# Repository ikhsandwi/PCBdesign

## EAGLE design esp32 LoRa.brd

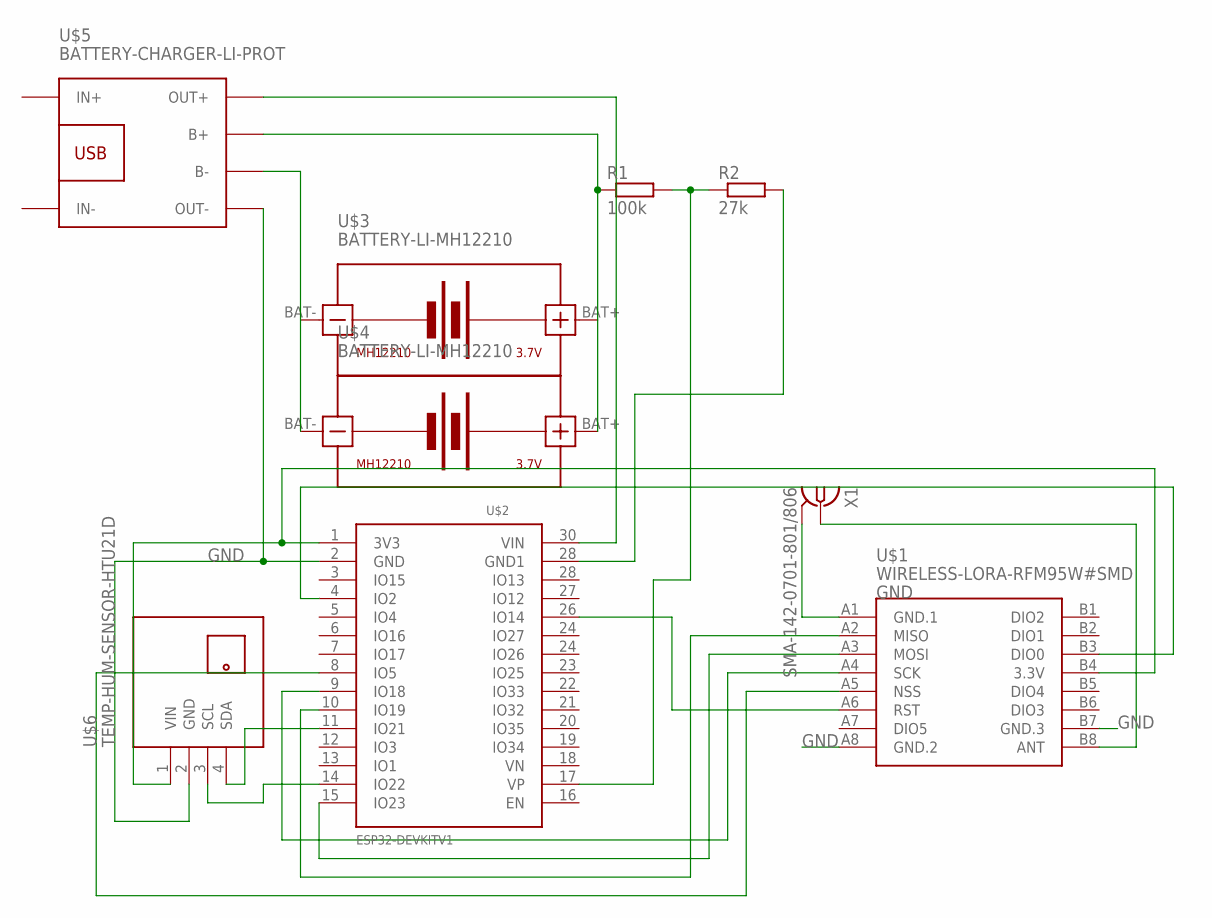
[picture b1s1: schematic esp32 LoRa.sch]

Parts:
R1: 100k; 0204/7
R2: 27k; 0204/7
U$1: WIRELESS-LORA-RFM95W#SMD
U$2: ESP32DEVKITV1; ESP32-DEVKITV1
U$3, U$4: BATTERY-LI-MH12210
U$5: BATTERY-CHARGER-LI-PROT
U$6: TEMP-HUM-SENSOR-HTU21D
X1: SMA-142-0701-801/806; J502-ND-142-0701-801/806

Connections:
GND: U$1.A1 (GND.1), U$1.A8 (GND.2), U$1.B7 (GND.3), U$2.2 (GND), U$5.OUT-, U$6.2 (GND), X1.G@1 (2), X1.G@2 (2), X1.G@3 (2), X1.G@4 (2)
unnamed: U$1.B4 (3.3V), U$2.1 (3V3), U$6.1 (VIN)
unnamed: R2.2, U$2.28 (IO13)
unnamed: U$2.14 (IO22), U$6.3 (SCL)
unnamed: U$2.11 (IO21), U$6.4 (SDA)
unnamed: U$3.BAT-, U$4.BAT-, U$5.B-
unnamed: R1.1, U$3.BAT+, U$4.BAT+, U$5.B+
unnamed: U$2.30 (VIN), U$5.OUT+
unnamed: U$1.A2 (MISO), U$2.10 (IO19)
unnamed: U$1.A3 (MOSI), U$2.15 (IO23)
unnamed: U$1.A4 (SCK), U$2.9 (IO18)
unnamed: U$1.B3 (DIO0), U$2.4 (IO2)
unnamed: U$1.A6 (RST), U$2.26 (IO14)
unnamed: U$1.A5 (NSS), U$2.8 (IO5)
unnamed: U$1.B8 (ANT), X1.1
unnamed: R1.2, R2.1, U$2.17 (VP)

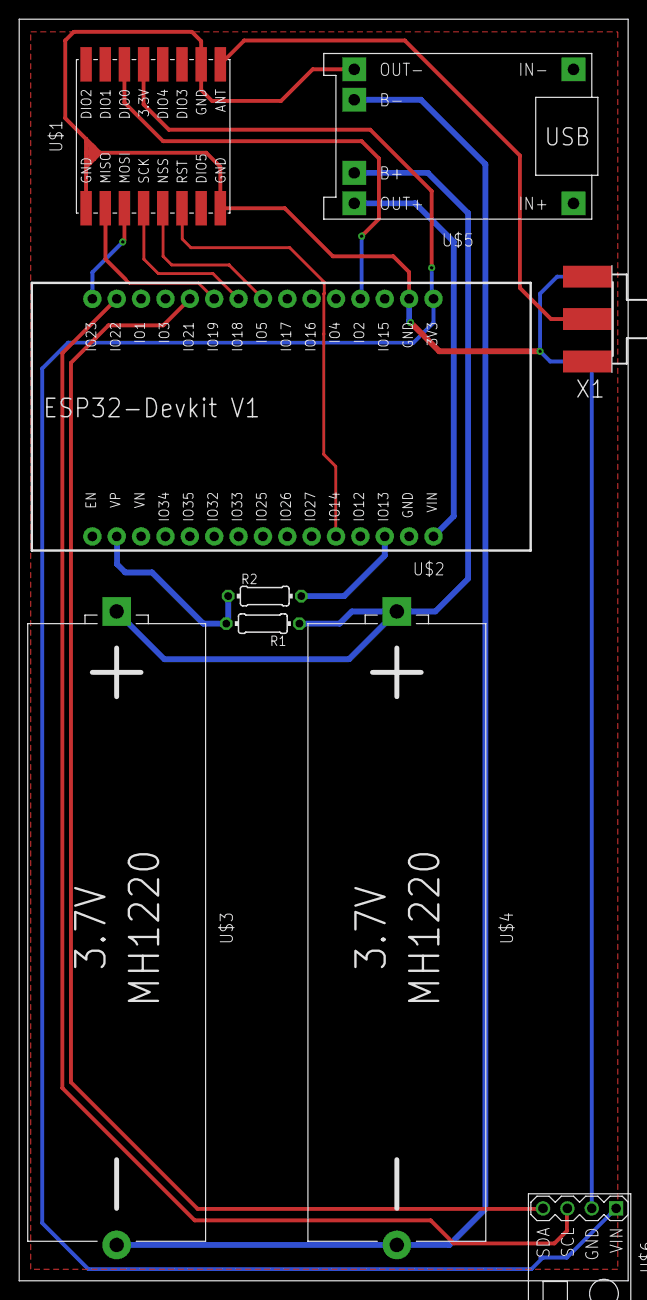
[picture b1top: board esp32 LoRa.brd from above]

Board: 2 copper layers, 63.5 x 131.5 mm, 9 parts (0 on the bottom side), 16 nets.

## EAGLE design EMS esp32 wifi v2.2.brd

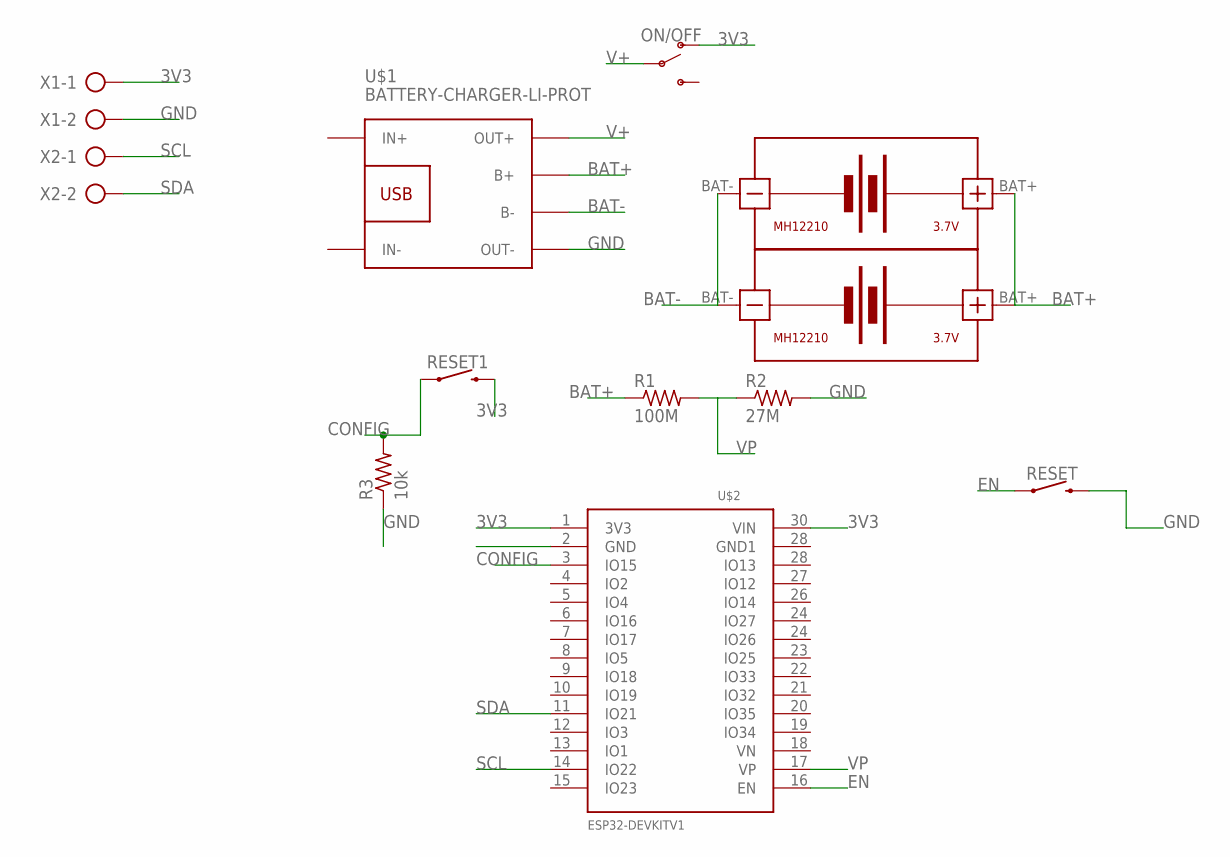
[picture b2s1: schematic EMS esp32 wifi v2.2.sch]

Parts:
ON/OFF: SWITCH-SPDT-PTH-11.6X4.0MM; SWITCH_SPDT_PTH_11.6X4.0MM
R1: 100M; 0204/7
R2: 27M; 0204/7
R3: 10k; 0204/7
RESET, RESET1: MOMENTARY-SWITCH-SPST-PTH-6.0MM; TACTILE_SWITCH_PTH_6.0MM
U$1: BATTERY-CHARGER-LI-PROT
U$2: ESP32DEVKITV1; ESP32-DEVKITV1
U$3, U$4: BATTERY-LI-MH12210
X1, X2: AK500/2

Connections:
3V3: ON/OFF.1 (O), RESET1.3 (2), U$2.1 (3V3), U$2.30 (VIN), X1.1
BAT+: R1.1, U$1.B+, U$3.BAT+, U$4.BAT+
BAT-: U$1.B-, U$3.BAT-, U$4.BAT-
CONFIG: R3.2, RESET1.1, U$2.3 (IO15)
EN: RESET.1, U$2.16 (EN)
GND: R2.2, R3.1, RESET.3 (2), U$1.OUT-, U$2.2 (GND), X1.2
SCL: U$2.14 (IO22), X2.1
SDA: U$2.11 (IO21), X2.2
V+: ON/OFF.2, U$1.OUT+
VP: R1.2, R2.1, U$2.17 (VP)

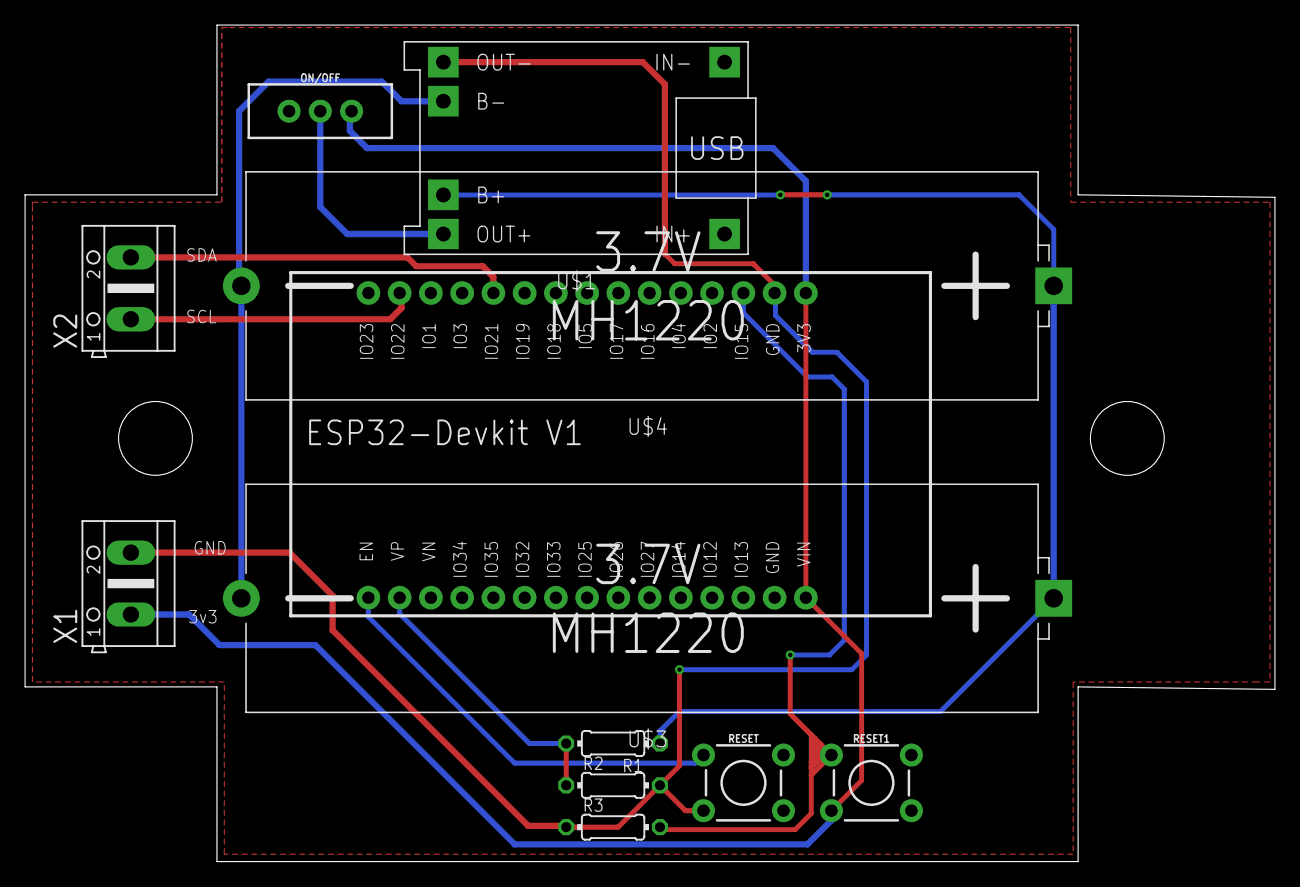
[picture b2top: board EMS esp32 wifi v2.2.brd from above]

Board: 2 copper layers, 101.6 x 68.0 mm, 12 parts (0 on the bottom side), 10 nets.

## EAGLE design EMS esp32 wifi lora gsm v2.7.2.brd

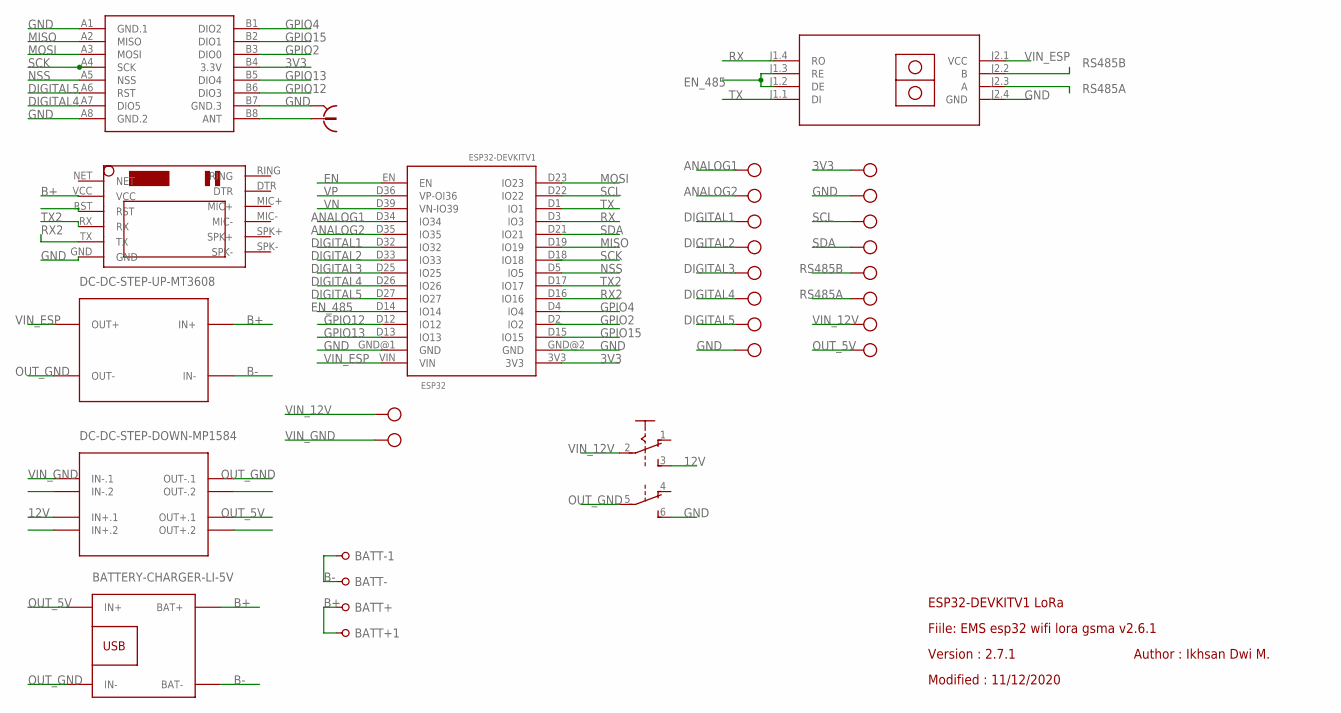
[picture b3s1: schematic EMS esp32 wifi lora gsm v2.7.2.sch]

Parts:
3V3__GND, 12V__5V: MKDSN1,5/2-5,08
A1__A2: MKDSN1,5/2-5,08
A_____B: MKDSN1,5/2-5,08
BATT+, BATT+1: PIN-1X1_2.00; 1X01M
BATT-, BATT-1: PIN-1X1; 1X01NONAME
D1__D2, D3__D4, D5_GND: MKDSN1,5/2-5,08
ESP32: ESP32DEVKITV1; ESP32-DEVKITV1
S1: A68-A31
SCL__SDA: MKDSN1,5/2-5,08
U$1: RS485-TTL-CONVERTER
U$2: DC-DC-STEP-UP-MT3608
U$3: DC-DC-STEP-DOWN-MP1584
U$4: BATTERY-CHARGER-LI-5V
U$5: WIRELESS-LORA-RFM95W#SMD
U$9: SIM800LMODULE
X1: 734120110
X10: MKDSN1,5/2-5,08

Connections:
3V3: 3V3__GND.1, ESP32.3V3, U$5.B4 (3.3V)
12V: S1.3 (S), U$3.IN+.1
ANALOG1: A1__A2.1, ESP32.D34 (IO34)
ANALOG2: A1__A2.2, ESP32.D35 (IO35)
B+: BATT+.1, BATT+1.1, U$2.IN+, U$4.BAT+, U$9.VCC
B-: BATT-.1, BATT-1.1, U$2.IN-, U$4.BAT-
DIGITAL1: D1__D2.1, ESP32.D32 (IO32)
DIGITAL2: D1__D2.2, ESP32.D33 (IO33)
DIGITAL3: D3__D4.1, ESP32.D25 (IO25)
DIGITAL4: D3__D4.2, ESP32.D26 (IO26), U$5.A7 (DIO5)
DIGITAL5: D5_GND.1, ESP32.D27 (IO27), U$5.A6 (RST)
EN: ESP32.EN
EN_485: ESP32.D14 (IO14), U$1.J1.2 (DE), U$1.J1.3 (RE)
GND: 3V3__GND.2, D5_GND.2, ESP32.GND@1 (GND), ESP32.GND@2 (GND), S1.6 (S), U$1.J2.4 (GND), U$5.A1 (GND.1), U$5.A8 (GND.2), U$5.B7 (GND.3), U$9.GND, X1.S@1 (2), X1.S@2 (2), X1.S@3 (2)
GPIO2: ESP32.D2 (IO2), U$5.B3 (DIO0)
GPIO4: ESP32.D4 (IO4), U$5.B1 (DIO2)
GPIO12: ESP32.D12 (IO12), U$5.B6 (DIO3)
GPIO13: ESP32.D13 (IO13), U$5.B5 (DIO4)
GPIO15: ESP32.D15 (IO15), U$5.B2 (DIO1)
MISO: ESP32.D19 (IO19), U$5.A2 (MISO)
MOSI: ESP32.D23 (IO23), U$5.A3 (MOSI)
unnamed: U$5.B8 (ANT), X1.1
NSS: ESP32.D5 (IO5), U$5.A5 (NSS)
OUT_5V: 12V__5V.2, U$3.OUT+.1, U$4.IN+
OUT_GND: S1.5, U$2.OUT-, U$3.OUT-.1, U$4.IN-
RS485A: A_____B.2, U$1.J2.3 (A)
RS485B: A_____B.1, U$1.J2.2 (B)
RX: ESP32.D3 (IO3), U$1.J1.4 (RO)
RX2: ESP32.D16 (IO16), U$9.TX
SCK: ESP32.D18 (IO18), U$5.A4 (SCK)
SCL: ESP32.D22 (IO22), SCL__SDA.1
SDA: ESP32.D21 (IO21), SCL__SDA.2
TX: ESP32.D1 (IO1), U$1.J1.1 (DI)
TX2: ESP32.D17 (IO17), U$9.RX
VIN_12V: 12V__5V.1, S1.2, X10.1
VIN_ESP: ESP32.VIN, U$1.J2.1 (VCC), U$2.OUT+
VIN_GND: U$3.IN-.1, X10.2
VN: ESP32.D39 (VN-IO39)
VP: ESP32.D36 (VP-OI36)

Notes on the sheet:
ESP32-DEVKITV1 LoRa
Fiile: EMS esp32 wifi lora gsma v2.6.1
Version : 2.7.1
Modified : 11/12/2020
Author : Ikhsan Dwi M.

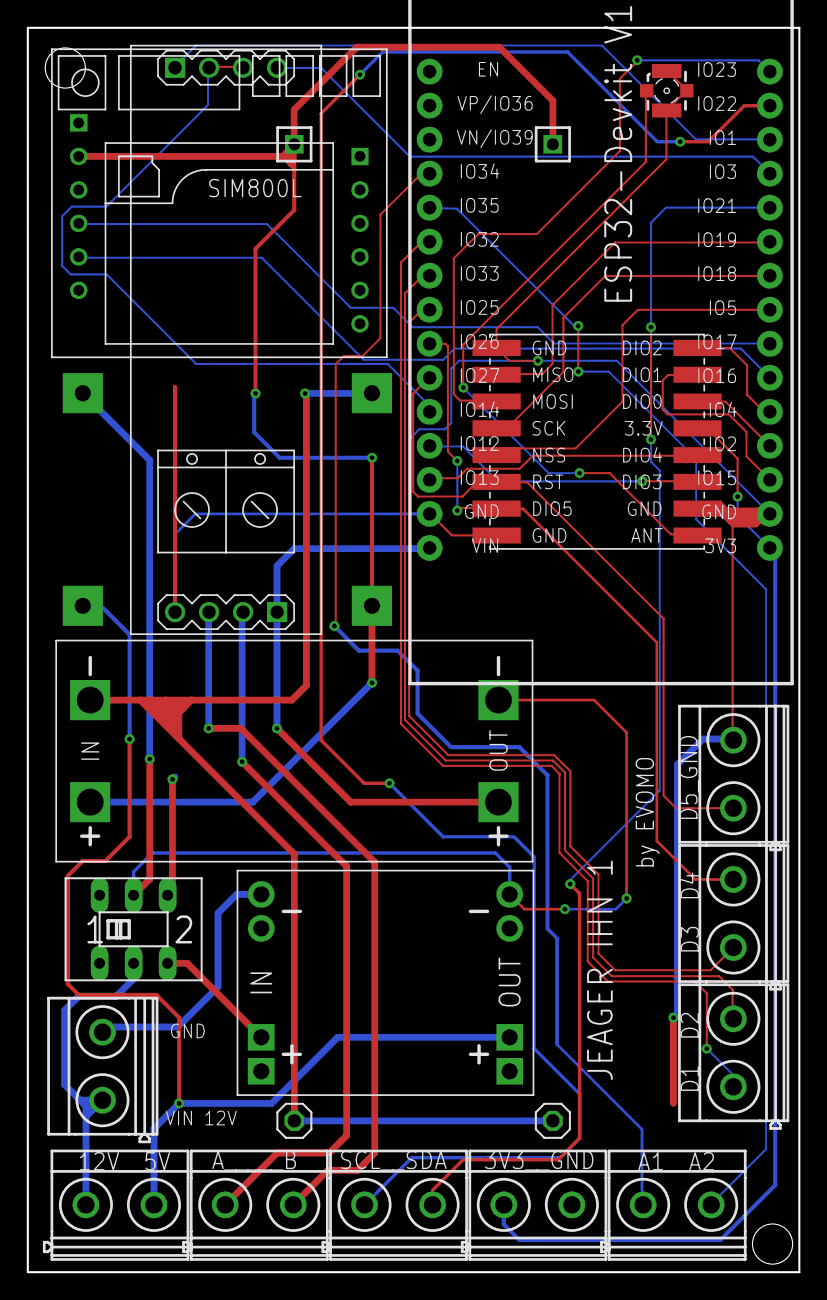
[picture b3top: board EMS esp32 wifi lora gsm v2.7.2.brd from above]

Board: 2 copper layers, 57.6 x 92.9 mm, 22 parts (1 on the bottom side), 36 nets.

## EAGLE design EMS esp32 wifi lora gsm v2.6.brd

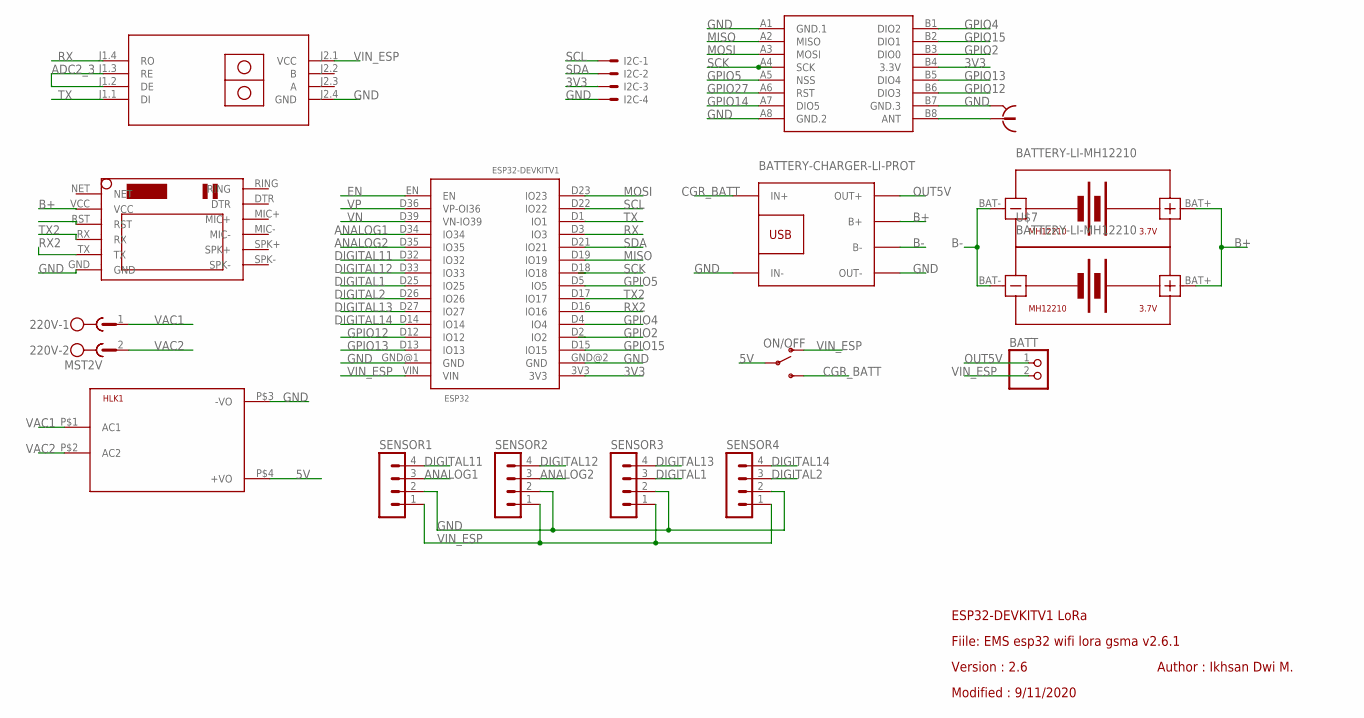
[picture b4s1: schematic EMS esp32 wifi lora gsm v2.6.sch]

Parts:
220V: MST2V; MSTBV2
BATT: PINHD-1X2; 1X02
ESP32: ESP32DEVKITV1; ESP32-DEVKITV1
HLK1: HLK-PM013W; HLK-PM01
I2C: 22-23-2041
ON/OFF: SWITCH-SPDT-PTH-11.6X4.0MM; SWITCH_SPDT_PTH_11.6X4.0MM
SENSOR1, SENSOR2, SENSOR3, SENSOR4: MA04-1
U$1: RS485-TTL-CONVERTER
U$5: WIRELESS-LORA-RFM95W#SMD
U$6, U$7: BATTERY-LI-MH12210
U$8: BATTERY-CHARGER-LI-PROT
U$9: SIM800LMODULE
X1: 734120110

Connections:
3V3: ESP32.3V3, I2C.3, U$5.B4 (3.3V)
5V: HLK1.P$4 (+VO), ON/OFF.2
ADC2_3: U$1.J1.2 (DE), U$1.J1.3 (RE)
ANALOG1: ESP32.D34 (IO34), SENSOR1.3
ANALOG2: ESP32.D35 (IO35), SENSOR2.3
B+: U$6.BAT+, U$7.BAT+, U$8.B+, U$9.VCC
B-: U$6.BAT-, U$7.BAT-, U$8.B-
CGR_BATT: ON/OFF.3 (S), U$8.IN+
DIGITAL1: ESP32.D25 (IO25), SENSOR3.3
DIGITAL2: ESP32.D26 (IO26), SENSOR4.3
DIGITAL11: ESP32.D32 (IO32), SENSOR1.4
DIGITAL12: ESP32.D33 (IO33), SENSOR2.4
DIGITAL13: ESP32.D27 (IO27), SENSOR3.4
DIGITAL14: ESP32.D14 (IO14), SENSOR4.4
EN: ESP32.EN
GND: ESP32.GND@1 (GND), ESP32.GND@2 (GND), HLK1.P$3 (-VO), I2C.4, SENSOR1.2, SENSOR2.2, SENSOR3.2, SENSOR4.2, U$1.J2.4 (GND), U$5.A1 (GND.1), U$5.A8 (GND.2), U$5.B7 (GND.3), U$8.IN-, U$8.OUT-, U$9.GND, X1.S@1 (2), X1.S@2 (2), X1.S@3 (2)
GPIO2: ESP32.D2 (IO2), U$5.B3 (DIO0)
GPIO4: ESP32.D4 (IO4), U$5.B1 (DIO2)
GPIO5: ESP32.D5 (IO5), U$5.A5 (NSS)
GPIO12: ESP32.D12 (IO12), U$5.B6 (DIO3)
GPIO13: ESP32.D13 (IO13), U$5.B5 (DIO4)
GPIO14: U$5.A7 (DIO5)
GPIO15: ESP32.D15 (IO15), U$5.B2 (DIO1)
GPIO27: U$5.A6 (RST)
MISO: ESP32.D19 (IO19), U$5.A2 (MISO)
MOSI: ESP32.D23 (IO23), U$5.A3 (MOSI)
unnamed: U$5.B8 (ANT), X1.1
OUT5V: BATT.1, U$8.OUT+
RX: ESP32.D3 (IO3), U$1.J1.4 (RO)
RX2: ESP32.D16 (IO16), U$9.TX
SCK: ESP32.D18 (IO18), U$5.A4 (SCK)
SCL: ESP32.D22 (IO22), I2C.1
SDA: ESP32.D21 (IO21), I2C.2
TX: ESP32.D1 (IO1), U$1.J1.1 (DI)
TX2: ESP32.D17 (IO17), U$9.RX
VAC1: 220V.1, HLK1.P$1 (AC1)
VAC2: 220V.2, HLK1.P$2 (AC2)
VIN_ESP: BATT.2, ESP32.VIN, ON/OFF.1 (O), SENSOR1.1, SENSOR2.1, SENSOR3.1, SENSOR4.1, U$1.J2.1 (VCC)
VN: ESP32.D39 (VN-IO39)
VP: ESP32.D36 (VP-OI36)

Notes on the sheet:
ESP32-DEVKITV1 LoRa
Fiile: EMS esp32 wifi lora gsma v2.6.1
Version : 2.6
Modified : 9/11/2020
Author : Ikhsan Dwi M.

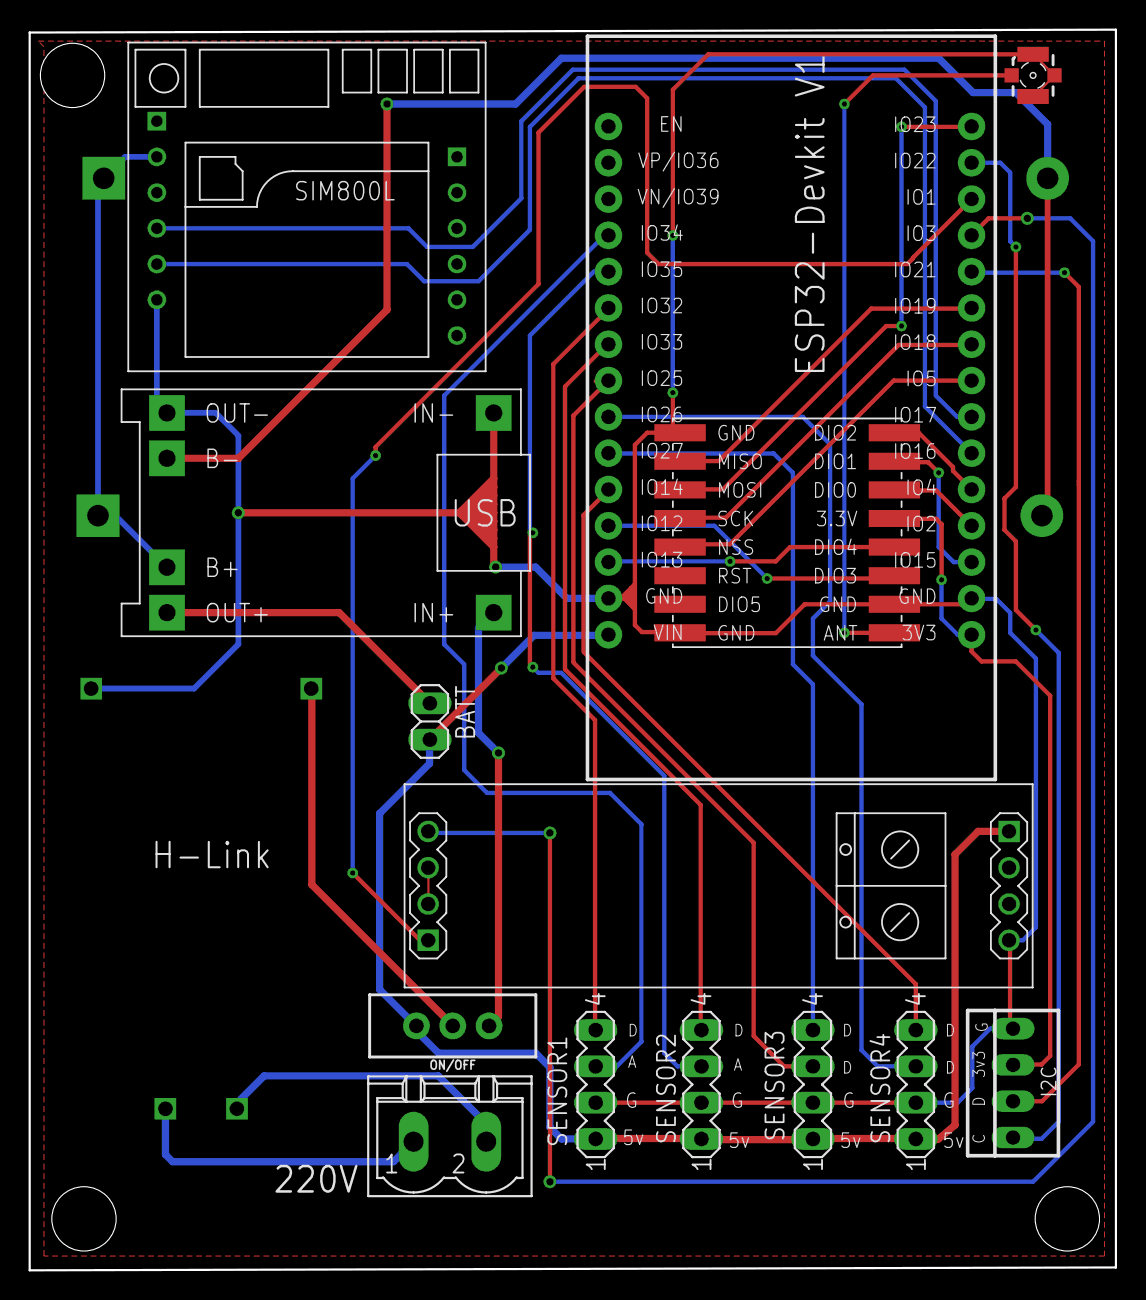
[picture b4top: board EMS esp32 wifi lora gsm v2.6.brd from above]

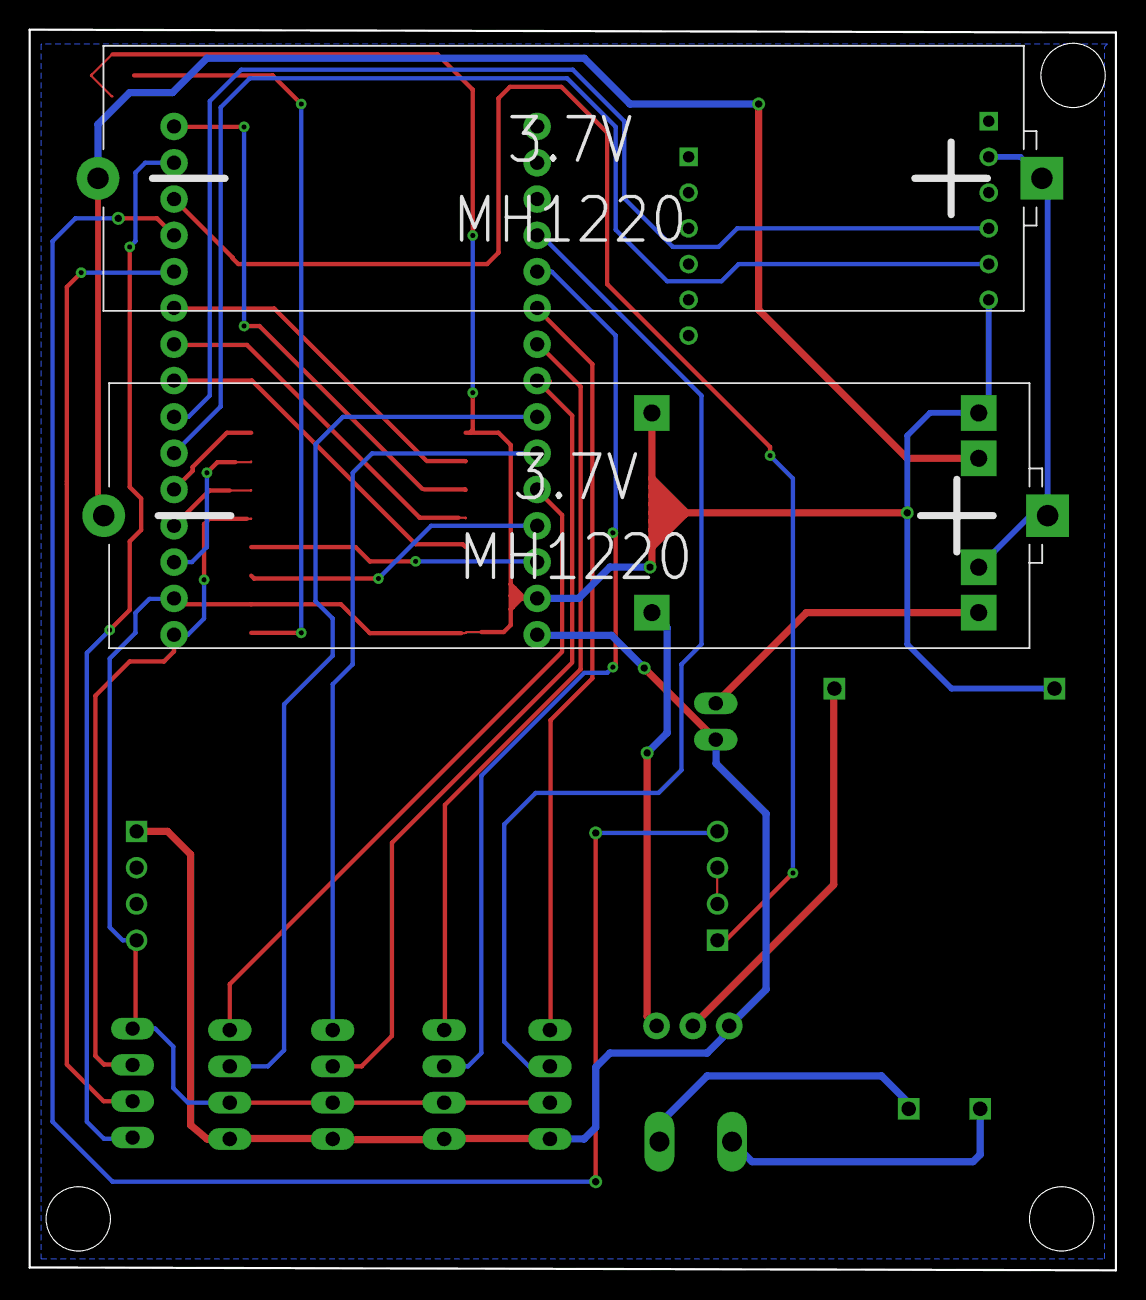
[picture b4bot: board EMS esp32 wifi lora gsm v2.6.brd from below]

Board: 2 copper layers, 76.0 x 86.8 mm, 17 parts (2 on the bottom side), 35 nets.

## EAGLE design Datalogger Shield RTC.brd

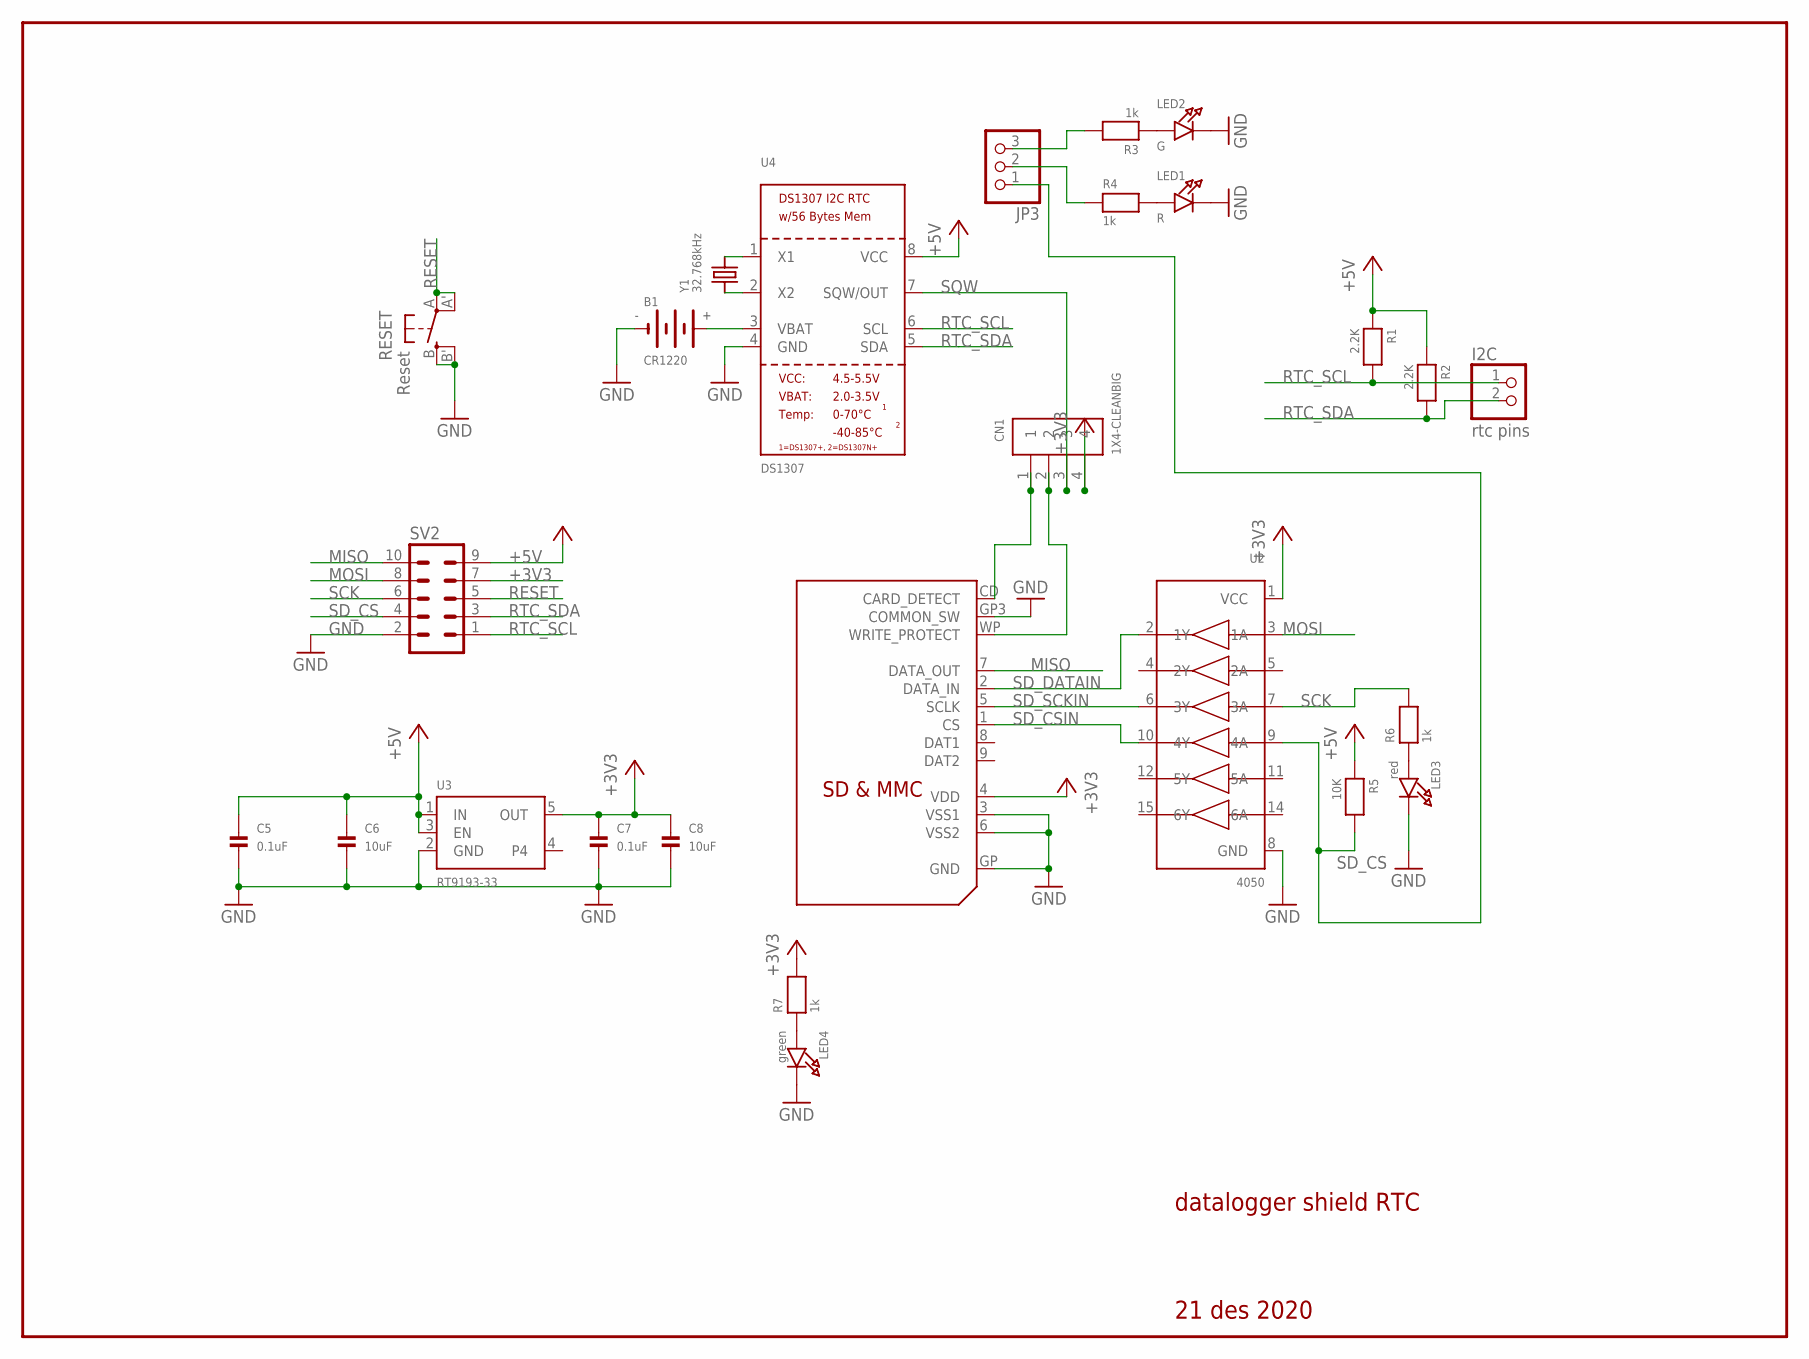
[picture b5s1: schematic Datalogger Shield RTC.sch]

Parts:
B1: CR1220
C5, C7: 0.1uF; 0805
C6, C8: 10uF; 0805
CN1: 1X4-CLEANBIG; 1X04-CLEANBIG
I2C: rtc pins; 1X02
JP3: HEADER-1X3ROUND; 1X03_ROUND
LED1: R; CHIPLED_0805
LED2: G; CHIPLED_0805
LED3: red; CHIPLED_0805
LED4: green; CHIPLED_0805
R1, R2: 2.2K; 0805
R3, R4, R6, R7: 1k; 0805
R5: 10K; 0805
RESET: Reset; EVQ-Q2
SV2: MA05-2
U2: 4050; SOIC16
U3: RT9193-33; SOT23-5
U4: DS1307; SOIC8_150MIL
U$2: SDMMC06132; 06132
Y1: 32.768kHz; CRYSTAL_8X3.8

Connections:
+3V3: C7.1, C8.1, CN1.4, R7.2, SV2.7, U2.1 (VCC), U3.5 (OUT), U$2.4 (VDD)
+5V: C5.1, C6.1, R1.1, R2.1, R5.1, SV2.9, U3.1 (IN), U3.3 (EN), U4.8 (VCC)
GND: B1.-, C5.2, C6.2, C7.2, C8.2, LED1.C, LED2.C, LED3.C, LED4.C, RESET.B (S), RESET.B' (S1), SV2.2, U2.8 (GND), U3.2 (GND), U4.4 (GND), U$2.3 (VSS1), U$2.6 (VSS2), U$2.GP (GND), U$2.GP3 (COMMON_SW)
MISO: SV2.10, U$2.7 (DATA_OUT)
MOSI: SV2.8, U2.3 (1A)
unnamed: LED1.A, R4.2
unnamed: U4.2 (X2), Y1.P$1 (1)
unnamed: U4.1 (X1), Y1.P$4 (2)
unnamed: LED2.A, R3.1
unnamed: LED3.A, R6.1
unnamed: B1.+$1 (+), U4.3 (VBAT)
unnamed: JP3.3, R3.2
unnamed: JP3.2, R4.1
unnamed: LED4.A, R7.1
RESET: RESET.A, RESET.A' (P1), SV2.5
RTC_SCL: I2C.1, R1.2, SV2.1, U4.6 (SCL)
RTC_SDA: I2C.2, R2.2, SV2.3, U4.5 (SDA)
SCK: R6.2, SV2.6, U2.7 (3A)
SD_CD: CN1.1, U$2.CD (CARD_DETECT)
SD_CS: JP3.1, R5.2, SV2.4, U2.9 (4A)
SD_CSIN: U2.10 (4Y), U$2.1 (CS)
SD_DATAIN: U2.2 (1Y), U$2.2 (DATA_IN)
SD_SCKIN: U2.6 (3Y), U$2.5 (SCLK)
SD_WP: CN1.2, U$2.WP (WRITE_PROTECT)
SQW: CN1.3, U4.7 (SQW/OUT)

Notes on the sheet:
datalogger shield RTC
21 des 2020

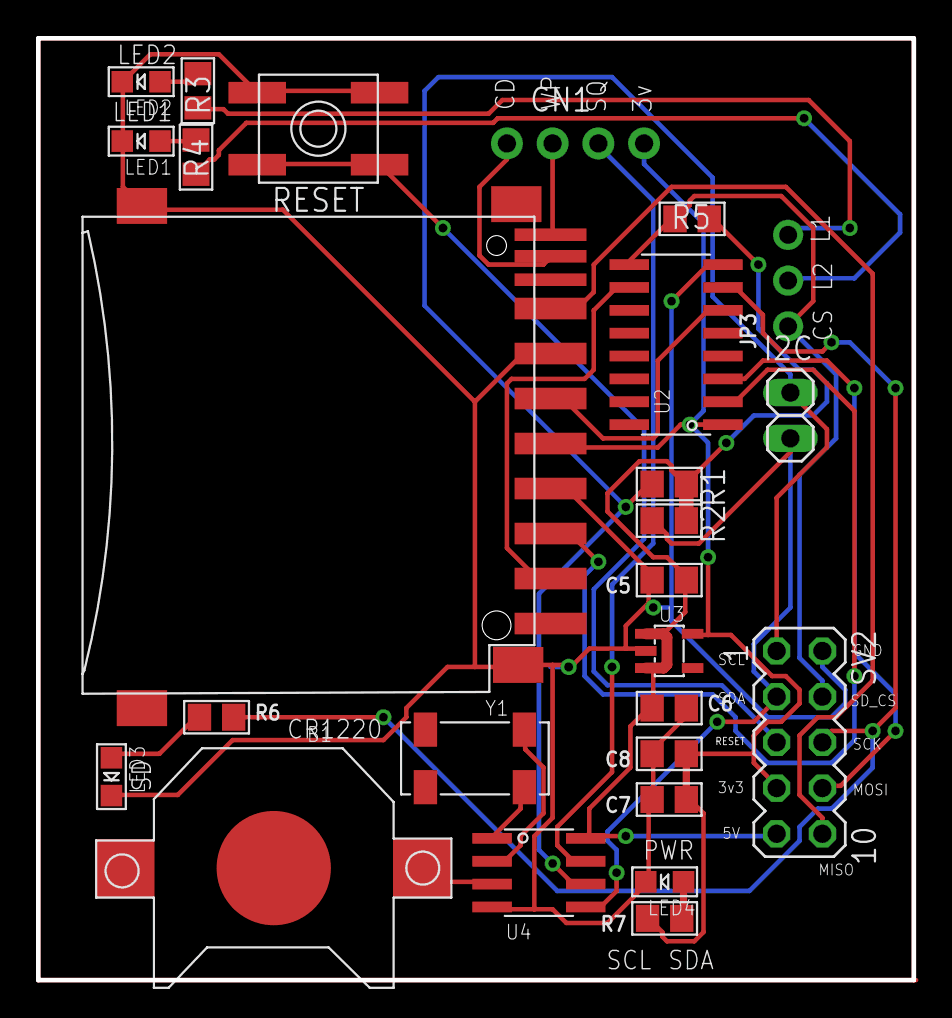
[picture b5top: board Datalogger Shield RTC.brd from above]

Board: 2 copper layers, 48.6 x 52.3 mm, 27 parts (1 on the bottom side), 25 nets.

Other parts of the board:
U$1: ADAFRUIT_TEXT_30MM

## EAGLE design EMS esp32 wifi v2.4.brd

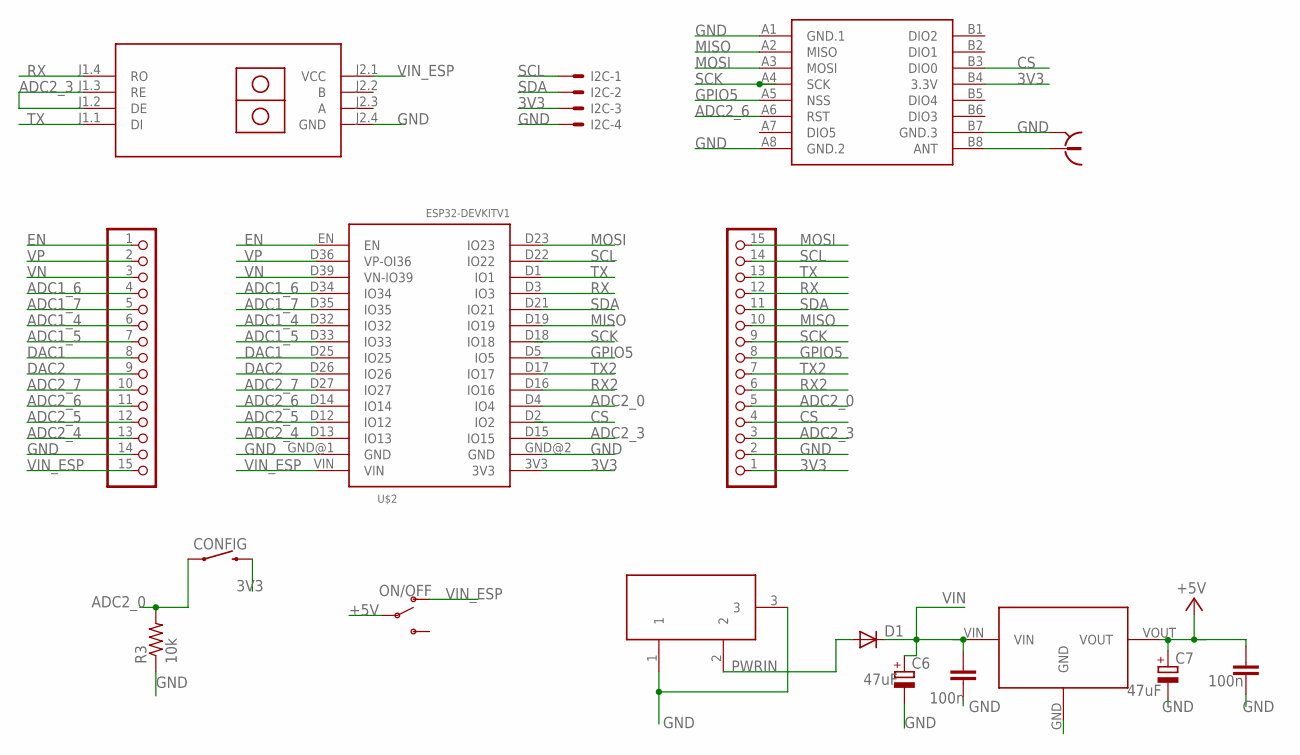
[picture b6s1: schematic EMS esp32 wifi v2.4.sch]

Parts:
C5, C14: 100n; C1206
C6, C7: 47uF; PANASONIC_D
CONFIG: MOMENTARY-SWITCH-SPST-PTH-6.0MM; TACTILE_SWITCH_PTH_6.0MM
D1: DIODE-SMB; SMB
I2C: 22-23-2041
JP1, JP2: PINHD-1X15; 1X15
ON/OFF: SWITCH-SPDT-PTH-11.6X4.0MM; SWITCH_SPDT_PTH_11.6X4.0MM
R3: 10k; 0204/7
RFM95: WIRELESS-LORA-RFM95W#SMD
U$1: RS485-TTL-CONVERTER
U$2: ESP32DEVKITV1; ESP32-DEVKITV1
U$3: SMARTPRJ_POWERSUPPLY_DC21MMX; SMARTPRJ_POWERSUPPLY_DC-21MM
U$4: 7805-TO263_7805; 7805-TO263_TO263
X1: 734120110

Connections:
3V3: CONFIG.3 (2), I2C.3, JP2.1, RFM95.B4 (3.3V), U$2.3V3
+5V: C7.+, C14.2, ON/OFF.2, U$4.VOUT
ADC1_4: JP1.6, U$2.D32 (IO32)
ADC1_5: JP1.7, U$2.D33 (IO33)
ADC1_6: JP1.4, U$2.D34 (IO34)
ADC1_7: JP1.5, U$2.D35 (IO35)
ADC2_0: CONFIG.1, JP2.5, R3.2, U$2.D4 (IO4)
ADC2_3: JP2.3, U$1.J1.2 (DE), U$1.J1.3 (RE), U$2.D15 (IO15)
ADC2_4: JP1.13, U$2.D13 (IO13)
ADC2_5: JP1.12, U$2.D12 (IO12)
ADC2_6: JP1.11, RFM95.A6 (RST), U$2.D14 (IO14)
ADC2_7: JP1.10, U$2.D27 (IO27)
CS: JP2.4, RFM95.B3 (DIO0), U$2.D2 (IO2)
DAC1: JP1.8, U$2.D25 (IO25)
DAC2: JP1.9, U$2.D26 (IO26)
EN: JP1.1, U$2.EN
GND: C5.1, C6.-, C7.-, C14.1, I2C.4, JP1.14, JP2.2, R3.1, RFM95.A1 (GND.1), RFM95.A8 (GND.2), RFM95.B7 (GND.3), U$1.J2.4 (GND), U$2.GND@1 (GND), U$2.GND@2 (GND), U$3.1, U$3.3, U$4.GND, X1.S@1 (2), X1.S@2 (2), X1.S@3 (2)
GPIO5: JP2.8, RFM95.A5 (NSS), U$2.D5 (IO5)
MISO: JP2.10, RFM95.A2 (MISO), U$2.D19 (IO19)
MOSI: JP2.15, RFM95.A3 (MOSI), U$2.D23 (IO23)
unnamed: RFM95.B8 (ANT), X1.1
PWRIN: D1.A, U$3.2
RX: JP2.12, U$1.J1.4 (RO), U$2.D3 (IO3)
RX2: JP2.6, U$2.D16 (IO16)
SCK: JP2.9, RFM95.A4 (SCK), U$2.D18 (IO18)
SCL: I2C.1, JP2.14, U$2.D22 (IO22)
SDA: I2C.2, JP2.11, U$2.D21 (IO21)
TX: JP2.13, U$1.J1.1 (DI), U$2.D1 (IO1)
TX2: JP2.7, U$2.D17 (IO17)
VIN: C5.2, C6.+, D1.C, U$4.VIN
VIN_ESP: JP1.15, ON/OFF.1 (O), U$1.J2.1 (VCC), U$2.VIN
VN: JP1.3, U$2.D39 (VN-IO39)
VP: JP1.2, U$2.D36 (VP-OI36)

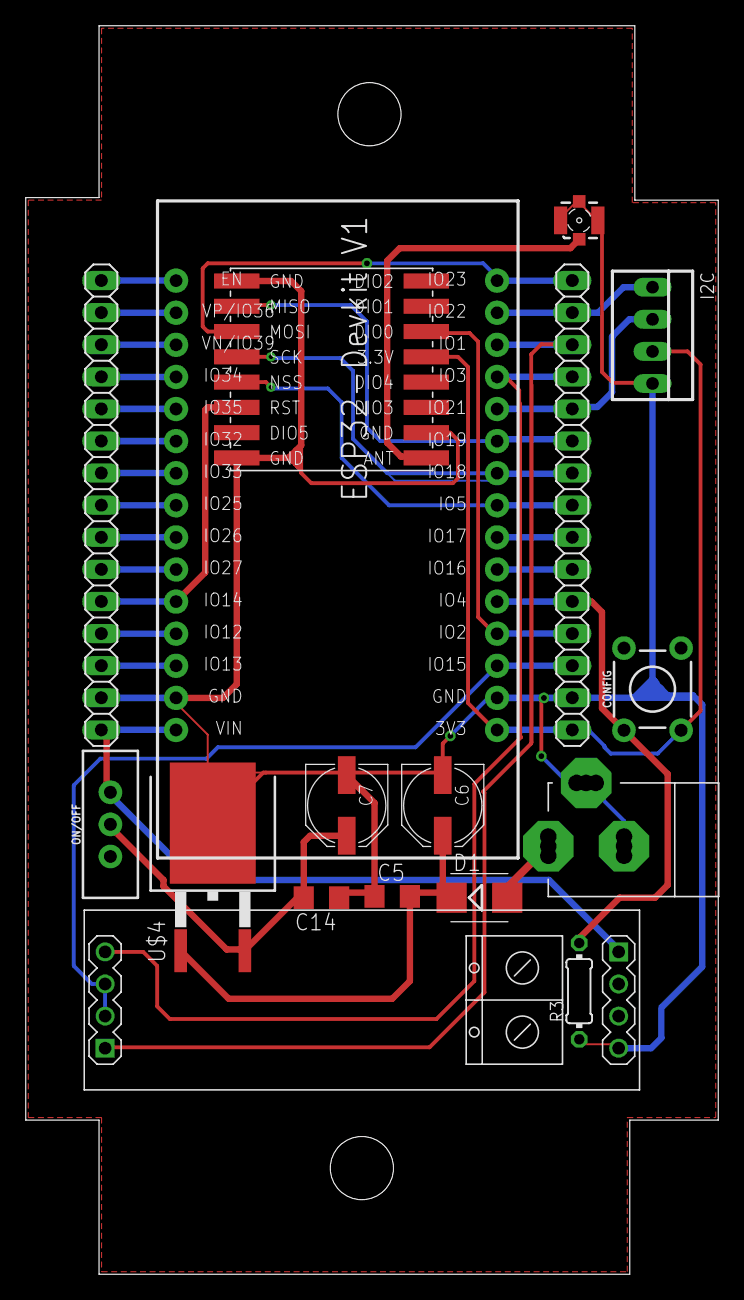
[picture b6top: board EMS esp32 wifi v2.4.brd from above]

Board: 2 copper layers, 54.8 x 98.8 mm, 17 parts (0 on the bottom side), 33 nets.

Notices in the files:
parts and their libraries:
diy-modules: Released under the Creative Commons Attribution 4.0 International License: http://creativecommons.org/licenses/by/4.0
SparkFun-Switches: Licensing: Creative Commons ShareAlike 4.0 International - https://creativecommons.org/licenses/by-sa/4.0
